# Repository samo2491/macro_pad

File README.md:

# 🛠️ CNC Macro Pad

A customizable **CNC Macro Pad** designed to speed up CNC workflows by providing dedicated physical buttons for common commands, macros, and shortcuts. Perfect for CNC routers, mills, laser cutters, and CAD/CAM software.

---

## ✨ Features

- ⌨️ Fully programmable macro keys  
- 🧠 Supports multi-key and layered macros  
- 🛠️ CNC-focused controls (Jog, Home, Zero, Start, Stop)  
- 🔌 USB HID (plug & play, no drivers required)  
- 🖥️ Cross-platform support (Windows, Linux, macOS)  
- 🔧 Open-source hardware and firmware  

---

## 📸 Preview

---

## 🧰 Hardware

- **Microcontroller:** seeed studio xiao rp2040
- **Keys:** 9  
- **Switches:** Tactile mx-style switches
- **screws** M3x16mm screws
- **Heatset insets** M3x5mx4mm
-  

---

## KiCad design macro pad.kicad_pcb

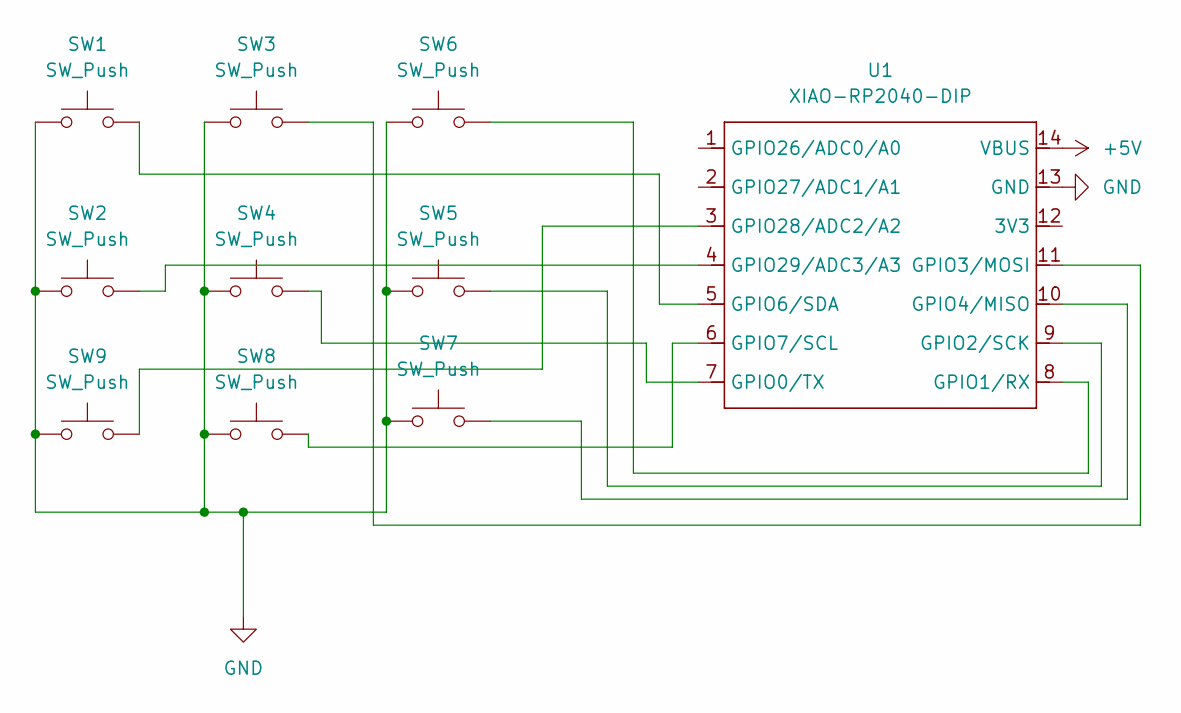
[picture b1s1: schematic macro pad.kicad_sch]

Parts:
SW1, SW2, SW3, SW4, SW5, SW6, SW7, SW8, SW9: SW_Push; SW_Cherry_MX_1.00u_PCB
U1: XIAO-RP2040-DIP

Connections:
+5V: U1.14 (VBUS)
GND: SW1.1, SW2.1, SW3.1, SW4.1, SW5.1, SW6.1, SW7.1, SW8.1, SW9.1, U1.13 (GND)
unnamed: SW4.2, U1.7 (GPIO0/TX)
unnamed: SW6.2, U1.8 (GPIO1/RX)
unnamed: SW5.2, U1.9 (GPIO2/SCK)
unnamed: SW3.2, U1.11 (GPIO3/MOSI)
unnamed: SW7.2, U1.10 (GPIO4/MISO)
unnamed: SW1.2, U1.5 (GPIO6/SDA)
unnamed: SW8.2, U1.6 (GPIO7/SCL)
unnamed: SW9.2, U1.3 (GPIO28/ADC2/A2)
unnamed: SW2.2, U1.4 (GPIO29/ADC3/A3)

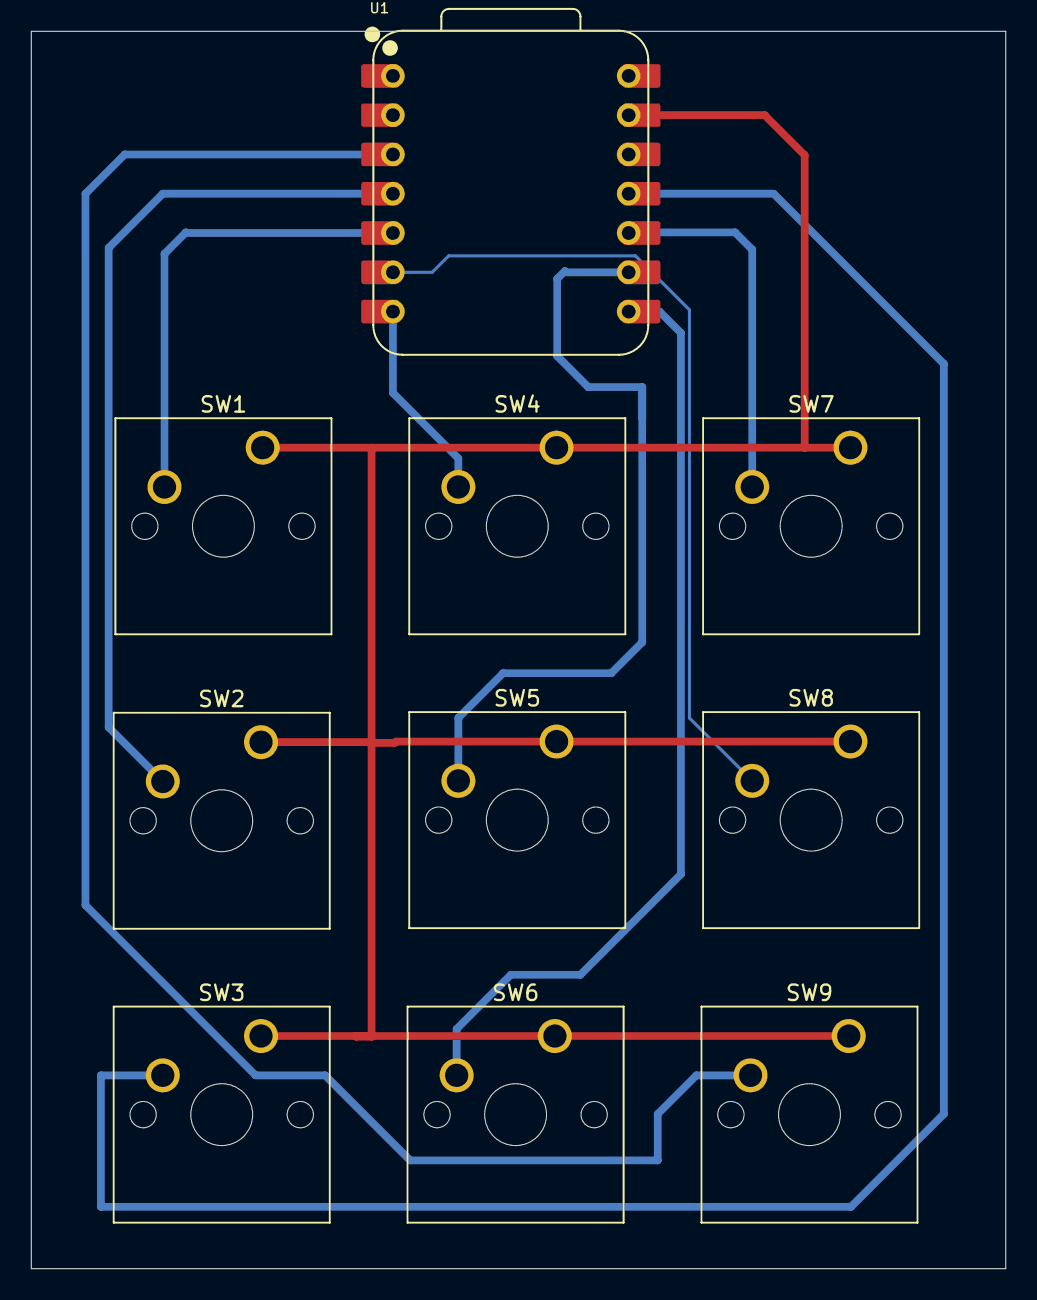
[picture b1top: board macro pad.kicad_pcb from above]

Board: 2 copper layers, 63.0 x 80.0 mm, 10 parts (0 on the bottom side), 10 nets.

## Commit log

2025-12-26 Revise README for CNC Macro Pad details
    Updated README to provide detailed information about the CNC Macro Pad, including features, hardware specifications, firmware, software compatibility, and contribution guidelines.
2025-12-26 Refactor README for improved clarity and structure
    Updated formatting and structure of the README file for clarity and consistency. Enhanced feature descriptions and added sections for hardware and firmware details.
2025-12-26 Revise hardware details and clean up firmware section
    Updated hardware specifications and removed flashing firmware example.
2025-12-26 Update README with images and hardware details
    Added images to the preview section and updated hardware specifications.
2025-12-27 Remove firmware section from README
    Removed firmware section and related details from README.
